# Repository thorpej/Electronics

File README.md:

# Electronics
thorpej's electronics projects repository.  Tube audio, other tube stuff, and stuff with computers in it.

# **WARNING**
Some of the materials in this repository desribe circuits that employ **HIGH VOLTAGES** that can be **LETHAL**.
If you build or otherwise use any of these circuits, you do so **AT YOUR OWN RISK**.

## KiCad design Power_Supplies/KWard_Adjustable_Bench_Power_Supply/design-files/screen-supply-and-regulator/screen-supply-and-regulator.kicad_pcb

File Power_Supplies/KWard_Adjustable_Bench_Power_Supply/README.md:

# Adjustable Bench Power Supply

This is a slight variation on an adjustable regulated bench power supply developed by
Kevin Ward and [documented on the AudioKarma forums](http://audiokarma.org/forums/index.php?threads/adjustable-bench-power-supply-redux.748700/)

The design is essentialy a Maida-style floating regulator that uses an array of 6550 pentodes
as the pass elements rather than a Darlington voltage follower as in the original Maida tech
note.  The 6550s also require a power supply for their screens, which also floats on the B+
rail's output voltage.  A major advantage of using pentode pass elements is the ability to
current-limit the supply, which is a natural result of how pentodes operate.  The current limit
could be adjusted by adjusting the 6550 screen supply voltage, although this feature is not
offered in this build.

There is also a current-limited negative bias supply that provides a nominal 0 - -100V adjustable
voltage range, in addition to an AC filament supply that can provide either 6.3Vac or 12.6Vac.

The main differences between this and Kevin's version are the transformers used.  Kevin's
build uses an Edcor XPWR133 for the B+ rail, floating 6550 screen supply, and the 6550 array's
heaters.  In my build, an AnTek AS-4T400 is used, which necessitates a separate transformer
for the floating 6550 screen supply.  I also opted to use a different transformer for the C-
rail.  Additionally, there are some minor improvements, such as the use of a precision 10-turn
pot for the B+ voltage control (to address a design flaw in the original), as well as an
provision to discharge capacitors on the device-under-test.  The design is otherwise un-changed from Kevin's design.

The interesting files here are:

	1. B+Supply.asc: LTSpice simulation of the B+ rail with the adjustments necessary for the choke and transformer differences.
	2. ScreenSupply.asc: LTSpice simulation of the floating 6550 screen supply with adjustments necessary for a Triad F6-120 transformer.
	3. BiasSupply.asc: LTSpice simulation of the C- rail with adjustments necessary for a Triad F4-120 transformer.
	
The remaining materials are either directly from the AudioKarma thread about Kevin's work (copied
locally for convenience) or Spice models needed for the simulations.

To be added in the future:

	1. Chassis layout drawings.
	2. Control panel CAD file for submitting to Front Panel Express.
	3. Descriptions / photographs of the hand-wired circuit boards.  (What a pain; I should have done proper PCBs...)

## ADDENDUM

I am going to be rebuilding this project using proper PCBs!  Watch here for the KiCad design files!

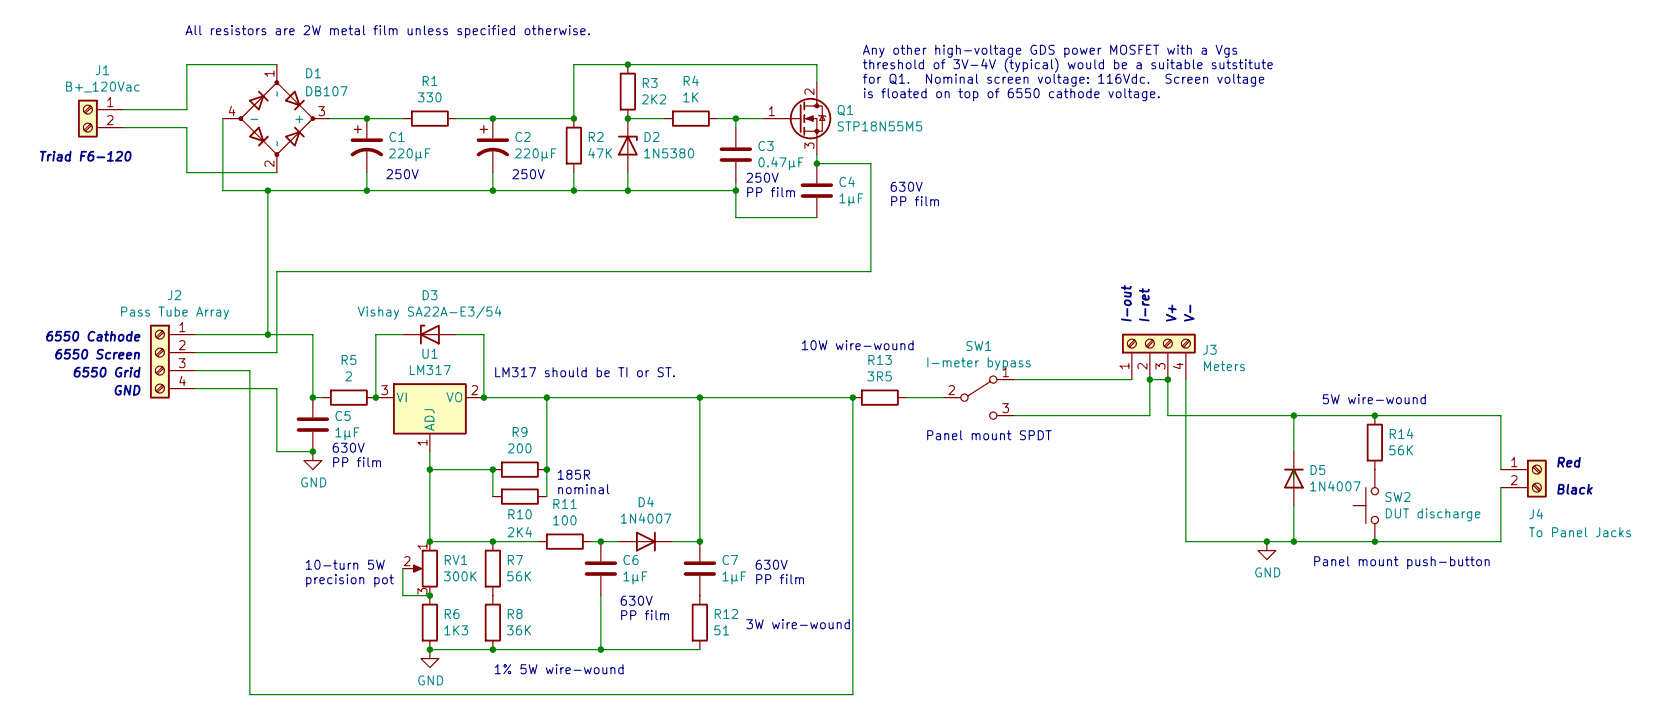
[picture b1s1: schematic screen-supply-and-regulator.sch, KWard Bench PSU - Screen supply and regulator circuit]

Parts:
C1, C2: 220µF; CP_Radial_D18.0mm_P7.50mm; Mouser 647-UCS2E221MHD
C3: 0.47µF; C_Rect_L18.0mm_W8.0mm_P15.00mm_FKS3_FKP3; Mouser 80-PHE426HB6470JR06
C4, C5, C6, C7: 1µF; C_Rect_L18.0mm_W18.0mm_P15.0mm; Mouser 667-ECW-FD2J105PC
D1: DB107; Diode_Bridge_DIP-4_W7.62mm_P5.08mm
D2: 1N5380; D_DO-201_P15.24mm_Horizontal
D3: Vishay SA22A-E3/54; D_DO-15_P15.24mm_Horizontal; Mouser 625-SA22A-E3/54
D4, D5: 1N4007; D_DO-41_SOD81_P10.16mm_Horizontal
J1: B+_120Vac; TerminalBlock_bornier-2_P5.08mm
J2: Pass Tube Array; TE_AMP-4_P10.16mm
J3: Meters; TE_AMP-4_P10.16mm
J4: To Panel Jacks; TE_AMP-2_P10.16mm
Q1: STP18N55M5; TO-220-3_Vertical
R1: 330; R_Axial_DIN0411_L9.9mm_D3.6mm_P15.24mm_Horizontal; Mouser 594-5083NW330R0J
R2: 47K; R_Axial_DIN0411_L9.9mm_D3.6mm_P15.24mm_Horizontal; Mouser 594-5083NW47K00JA100
R3: 2K2; R_Axial_DIN0411_L9.9mm_D3.6mm_P15.24mm_Horizontal; Mouser 594-5083NW2K200J
R4: 1K; R_Axial_DIN0411_L9.9mm_D3.6mm_P15.24mm_Horizontal; Mouser 594-5083NW1K000J
R5: 2; R_Axial_DIN0411_L9.9mm_D3.6mm_P15.24mm_Horizontal; Mouser 594-5083NW2R000J
R6: 1K3; R_Axial_DIN0411_L9.9mm_D3.6mm_P15.24mm_Horizontal; Mouser 594-5083NW1K300J
R7: 56K; R_Axial_Power_L25.0mm_W9.0mm_P30.48mm; Mouser 71-RS00556K00FE12
R8: 36K; R_Axial_Power_L25.0mm_W9.0mm_P30.48mm; Mouser 71-RS00236K00FB12
R9: 200; R_Axial_DIN0411_L9.9mm_D3.6mm_P15.24mm_Horizontal; Mouser 594-5083NW200R0J
R10: 2K4; R_Axial_DIN0411_L9.9mm_D3.6mm_P15.24mm_Horizontal; Mouser 594-5083NW2K400J
R11: 100; R_Axial_DIN0411_L9.9mm_D3.6mm_P15.24mm_Horizontal; Mouser 594-5083NW100R0JA100
R12: 51; R_Axial_DIN0614_L14.3mm_D5.7mm_P20.32mm_Horizontal; Mouser 71-NS02B51R00FE12
R13: 3R5; R_Axial_Power_L48.0mm_W12.5mm_P55.88mm; Mouser 71-RS0103R500FE12
R14: 56K; R_Axial_Power_L25.0mm_W6.4mm_P30.48mm; Mouser 71-CW00556K00JE12
RV1: 300K; TE_AMP-3_P10.16mm
SW1: I-meter bypass; TerminalBlock_bornier-3_P5.08mm
SW2: DUT discharge; TE_AMP-2_P10.16mm
U1: LM317; TO-220-3_Vertical; Mouser 926-LM317AT/NOPB

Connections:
GND: C5.2, C6.2, D5.2 (A), J2.4, J3.4, J4.2, R6.2, R8.2, R12.2, SW2.1
unnamed: C1.1, D1.3 (+), R1.2
unnamed: C1.2, C2.2, C3.2, C4.2, C5.1, D1.4 (-), D2.2 (A), J2.1, R2.2, R5.2
unnamed: C2.1, Q1.2 (D), R1.1, R2.1, R3.1
unnamed: C3.1, Q1.1 (G), R4.1
unnamed: C4.1, J2.2, Q1.3 (S)
unnamed: C6.1, D4.2 (A), R11.1
unnamed: C7.1, D3.2 (A), D4.1 (K), J2.3, R9.1, R10.1, R13.2, U1.2 (VO)
unnamed: C7.2, R12.1
unnamed: D1.1 (~~), J1.1
unnamed: D1.2 (~~), J1.2
unnamed: D2.1 (K), R3.2, R4.2
unnamed: D3.1 (K), R5.1, U1.3 (VI)
unnamed: D5.1 (K), J3.2, J3.3, J4.1, R14.1, SW1.3 (C)
unnamed: J3.1, SW1.1 (A)
unnamed: R6.1, RV1.2, RV1.3
unnamed: R7.2, R8.1
unnamed: R7.1, R9.2, R10.2, R11.2, RV1.1, U1.1 (ADJ)
unnamed: R13.1, SW1.2 (B)
unnamed: R14.2, SW2.2

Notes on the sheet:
Triad F6-120
Any other high-voltage GDS power MOSFET with a Vgs threshold of 3V-4V (typical) would be a suitable sutstitute for Q1. Nominal screen voltage: 116Vdc. Screen voltage is floated on top of 6550 cathode voltage.
6550 Cathode
6550 Grid
6550 Screen
630V PP film
185R nominal
10-turn 5W precision pot
3W wire-wound
1% 5W wire-wound
LM317 should be TI or ST.
All resistors are 2W metal film unless specified otherwise.
10W wire-wound
5W wire-wound
Panel mount SPDT
Panel mount push-button
Red
Black
I-out
I-ret
250V
250V PP film
GND

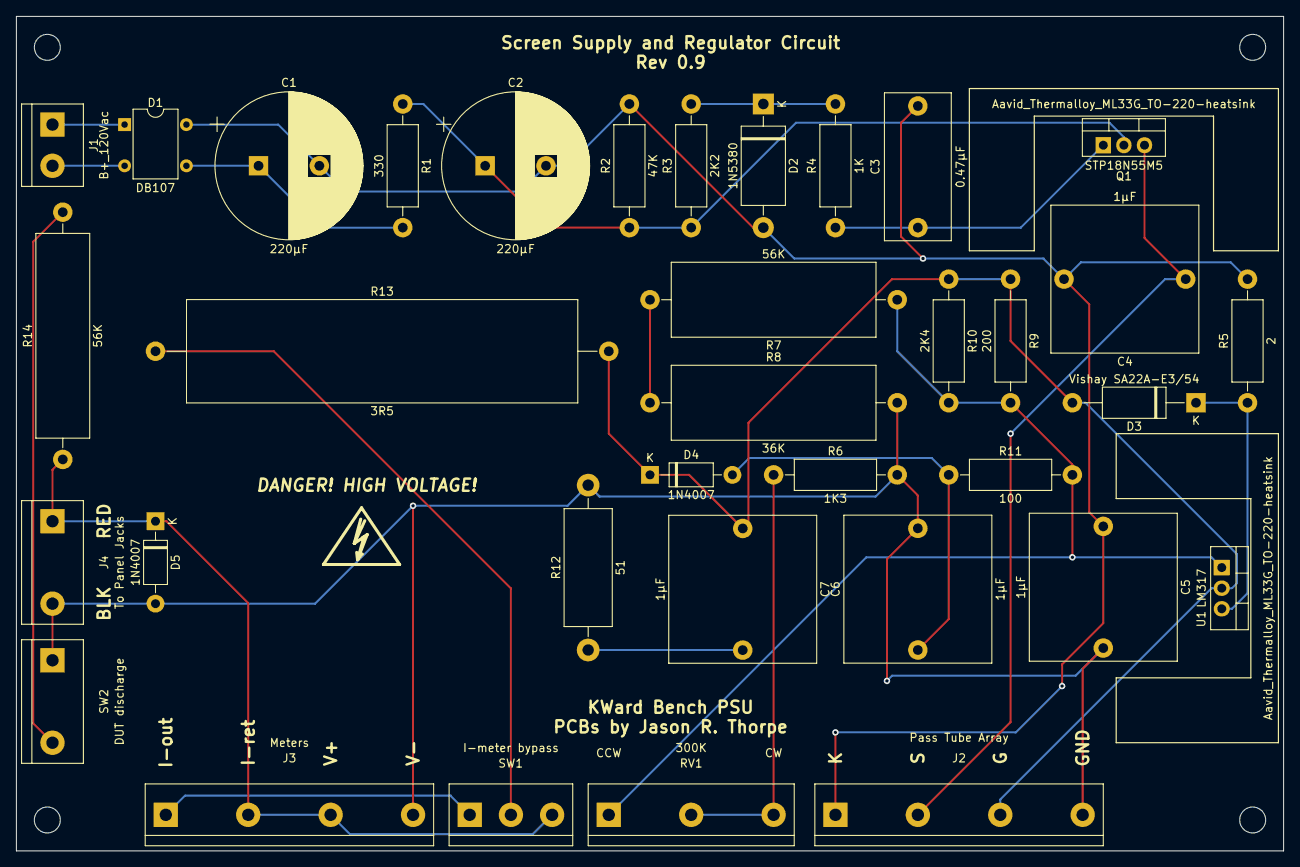
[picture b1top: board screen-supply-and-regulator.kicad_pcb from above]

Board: 2 copper layers, 156.2 x 102.9 mm, 35 parts (0 on the bottom side), 20 nets.

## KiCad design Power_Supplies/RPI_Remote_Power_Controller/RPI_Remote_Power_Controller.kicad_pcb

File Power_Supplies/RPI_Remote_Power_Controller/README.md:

# Remote Power Controller (controlled by Raspberry Pi)

**NOTE: This is provided for informational purposes only.  If you use this information,
or any of these design files, you do so at your own risk.**

This board is for, essentially, a remote-controlled power strip.  A Raspberry Pi Zero W (or a
Banana Pi M2 Zero) controls a Microchip MCP230008 I/O expander over I2C, which in turn drives
the outputs of a pair of ULN2003 Darlington arrays with open-collector outputs (7 on one, 1 on
the other, for a total of 8 outputs).  Each Darlington pair in the ULN2003 features a flyback
diode, making them suitable for driving inductive loads.

The ULN2003 outputs are connected to one end of the coil on a Rayex LB2-12DS-R DPDT relay, the other end being connected to a +12Vdc power supply.  The relay switches are connect to AC Mains input, switching both the hot and neutral leads.

A 12V - 5V @ 5A regulator provides power to the Raspberry Pi Zero W over the 40-pin GPIO header.
The regulator is attached to a relatively beefy Aavid ML33G heat sink.  A 2200µF reservoir
capacitor is provided to handle any transient current surges.

The console UART on the Raspberry Pi is brought out to a sepate 3-pin header on the board
for convenience.

The board will also accommodate a Banana Pi M2 Zero.  This board has the same basic footprint
as the Raspberry Pi Zero W, and also includes built-in WiFi.  The Banana Pi board also has
a compatible GPIO header.  _NOTE: The Banana Pi's console (debug) UART is routed to a separate
pin header on the Banana Pi itself; if you use a Banana Pi, you don't need to use the console
pin header on the power controller board; solder a pin header onto the Banana Pi board, and
use that for console I/O._.

The board's mains input should be fused with a 12A fuse, as that is the current rating of
the Rayex relays, and was used as a design parameter for the PCB.  The mains traces on the
PCB are capable of carrying a 12A load **_if and only if the board is fabricated with
2oz copper_**.  If the board is fabriacated with 1oz copper, then the mains input fuse should be limited to 6A.

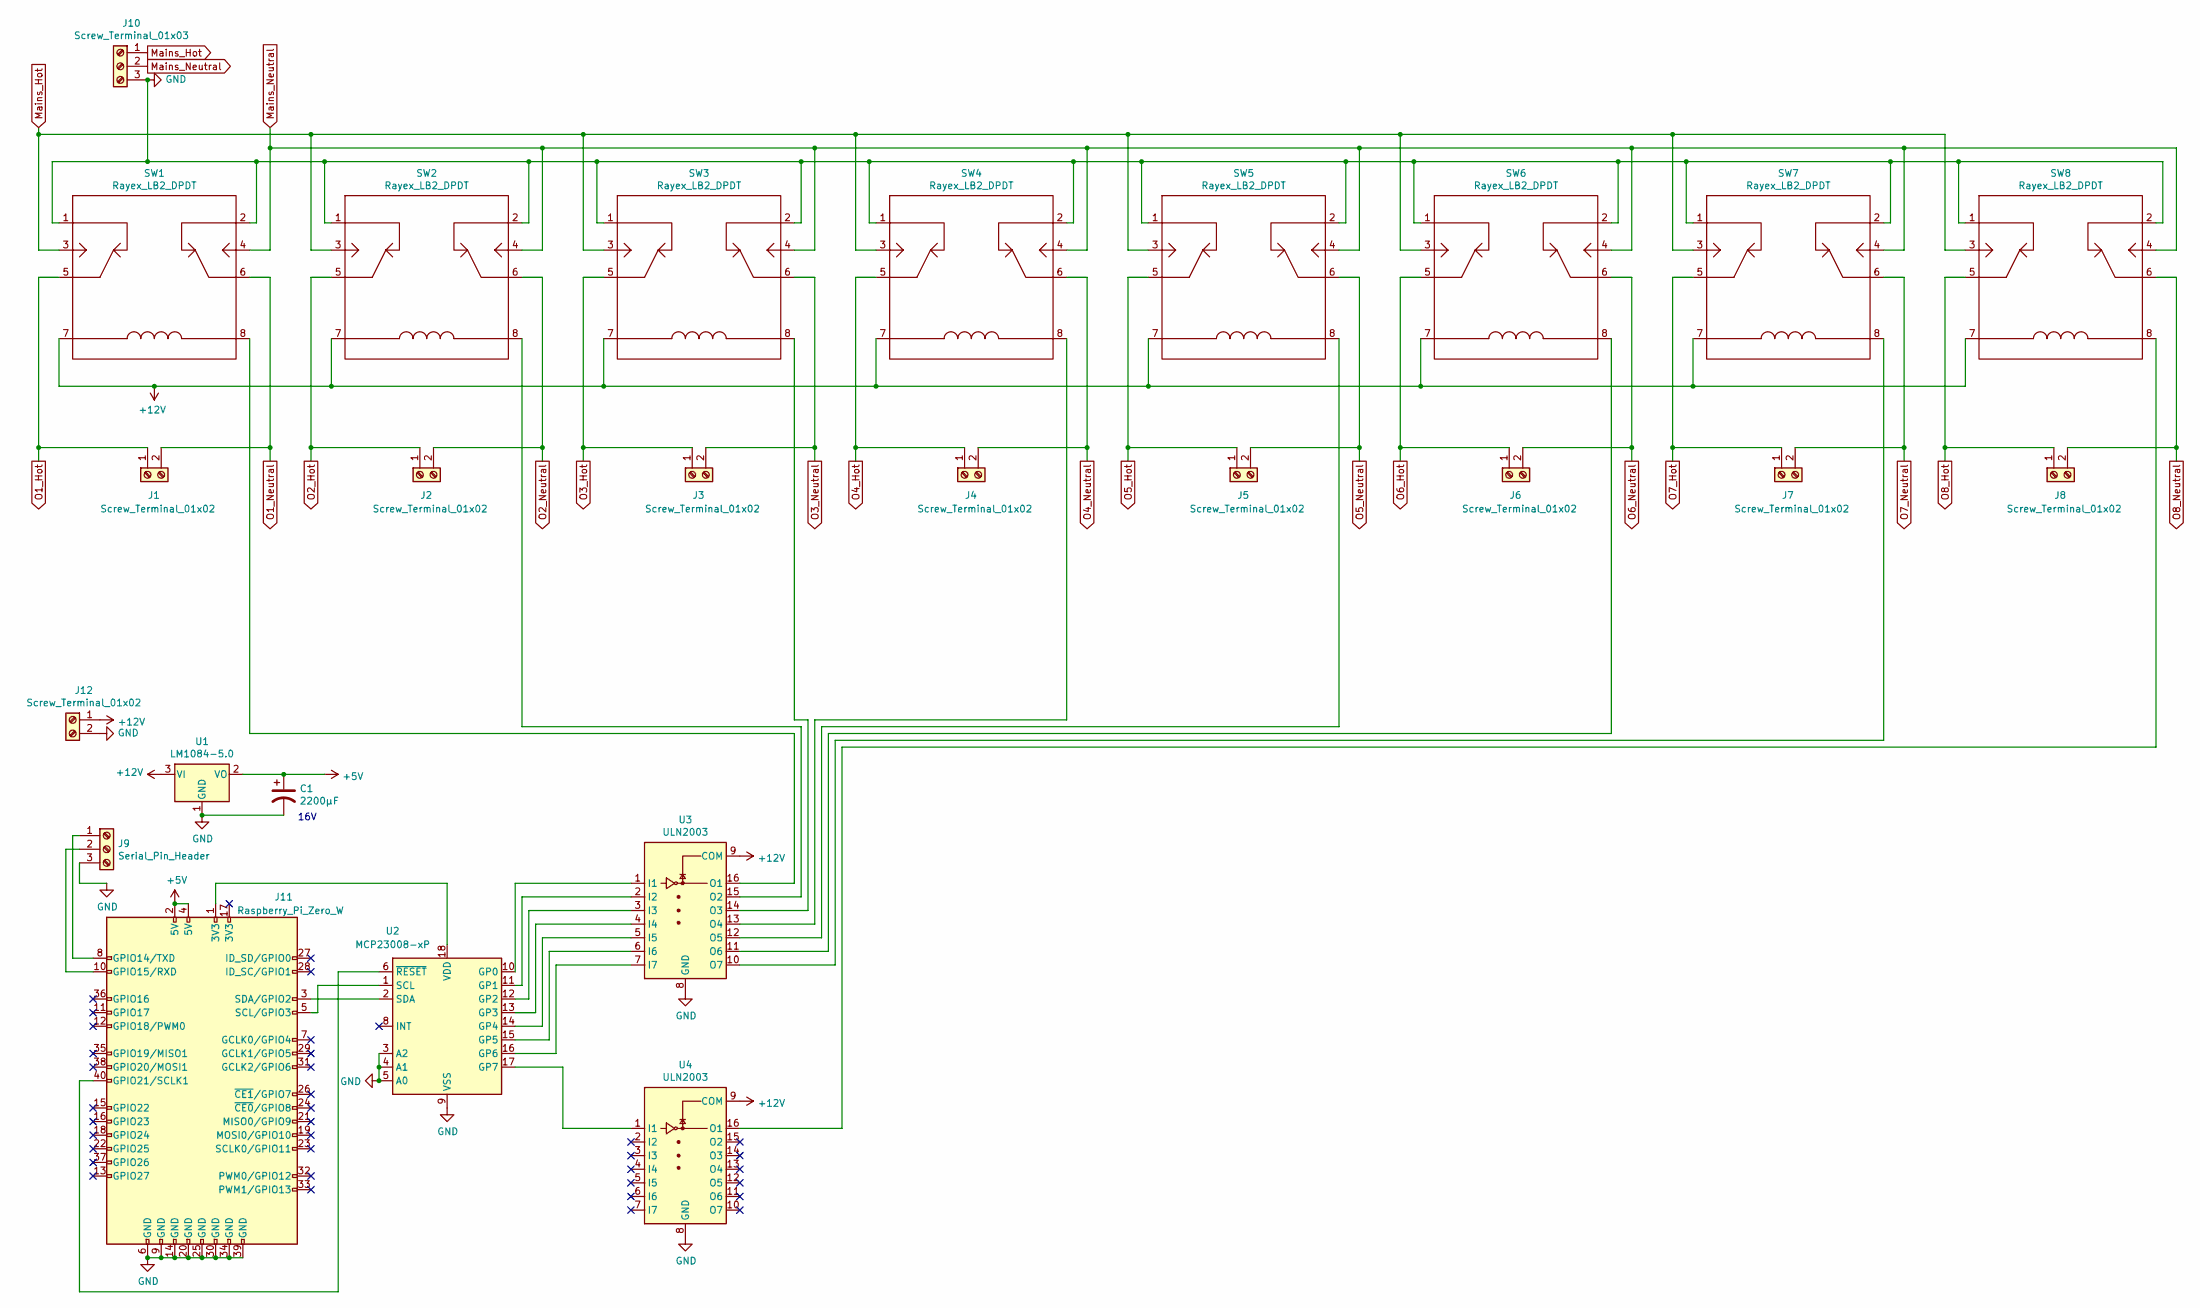
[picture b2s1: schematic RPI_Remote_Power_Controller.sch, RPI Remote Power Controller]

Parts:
C1: 2200µF; CP_Radial_D13.0mm_P5.00mm; Mouser 710-860040378015
J1, J2, J3, J4, J5, J6, J7, J8: Screw_Terminal_01x02; TE_AMP-2_P10.16mm
J9: Serial_Pin_Header; PinHeader_1x03_P2.54mm_Vertical
J10: Screw_Terminal_01x03; TE_AMP-3_P10.16mm
J11: Raspberry_Pi_Zero_W; PinHeader_2x20_P2.54mm_Vertical
J12: Screw_Terminal_01x02; TerminalBlock_bornier-2_P5.08mm
SW1, SW2, SW3, SW4, SW5, SW6, SW7, SW8: Rayex_LB2_DPDT; Rayex-LB2-lug
U1: LM1084-5.0; TO-220-3_Vertical
U2: MCP23008-xP; DIP-18_W7.62mm_Socket
U3, U4: ULN2003; DIP-16_W7.62mm_Socket

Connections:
+5V: C1.1, J11.2 (5V), J11.4 (5V), U1.2 (VO)
+12V: J12.1, SW1.7, SW2.7, SW3.7, SW4.7, SW5.7, SW6.7, SW7.7, SW8.7, U1.3 (VI), U3.9 (COM), U4.9 (COM)
GND: C1.2, J9.3, J10.3, J11.6 (GND), J11.9 (GND), J11.14 (GND), J11.20 (GND), J11.25 (GND), J11.30 (GND), J11.34 (GND), J11.39 (GND), J12.2, SW1.1, SW1.2, SW2.1, SW2.2, SW3.1, SW3.2, SW4.1, SW4.2, SW5.1, SW5.2, SW6.1, SW6.2, SW7.1, SW7.2, SW8.1, SW8.2, U1.1 (GND), U2.3 (A2), U2.4 (A1), U2.5 (A0), U2.9 (VSS), U3.8 (GND), U4.8 (GND)
Mains_Hot: J10.1, SW1.3, SW2.3, SW3.3, SW4.3, SW5.3, SW6.3, SW7.3, SW8.3
Mains_Neutral: J10.2, SW1.4, SW2.4, SW3.4, SW4.4, SW5.4, SW6.4, SW7.4, SW8.4
unnamed: J11.1 (3V3), U2.18 (VDD)
unnamed: J11.3 (SDA/GPIO2), U2.2 (SDA)
unnamed: J11.5 (SCL/GPIO3), U2.1 (SCL)
unnamed: J9.1, J11.8 (GPIO14/TXD)
unnamed: J9.2, J11.10 (GPIO15/RXD)
unnamed: J11.40 (GPIO21/SCLK1), U2.6 (~RESET)
unnamed: SW1.8, U3.16 (O1)
unnamed: SW2.8, U3.15 (O2)
unnamed: SW3.8, U3.14 (O3)
unnamed: SW4.8, U3.13 (O4)
unnamed: SW5.8, U3.12 (O5)
unnamed: SW6.8, U3.11 (O6)
unnamed: SW7.8, U3.10 (O7)
unnamed: SW8.8, U4.16 (O1)
unnamed: U2.10 (GP0), U3.1 (I1)
unnamed: U2.11 (GP1), U3.2 (I2)
unnamed: U2.12 (GP2), U3.3 (I3)
unnamed: U2.13 (GP3), U3.4 (I4)
unnamed: U2.14 (GP4), U3.5 (I5)
unnamed: U2.15 (GP5), U3.6 (I6)
unnamed: U2.16 (GP6), U3.7 (I7)
unnamed: U2.17 (GP7), U4.1 (I1)
O1_Hot: J1.1, SW1.5
O1_Neutral: J1.2, SW1.6
O2_Hot: J2.1, SW2.5
O2_Neutral: J2.2, SW2.6
O3_Hot: J3.1, SW3.5
O3_Neutral: J3.2, SW3.6
O4_Hot: J4.1, SW4.5
O4_Neutral: J4.2, SW4.6
O5_Hot: J5.1, SW5.5
O5_Neutral: J5.2, SW5.6
O6_Hot: J6.1, SW6.5
O6_Neutral: J6.2, SW6.6
O7_Hot: J7.1, SW7.5
O7_Neutral: J7.2, SW7.6
O8_Hot: J8.1, SW8.5
O8_Neutral: J8.2, SW8.6

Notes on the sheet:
16V

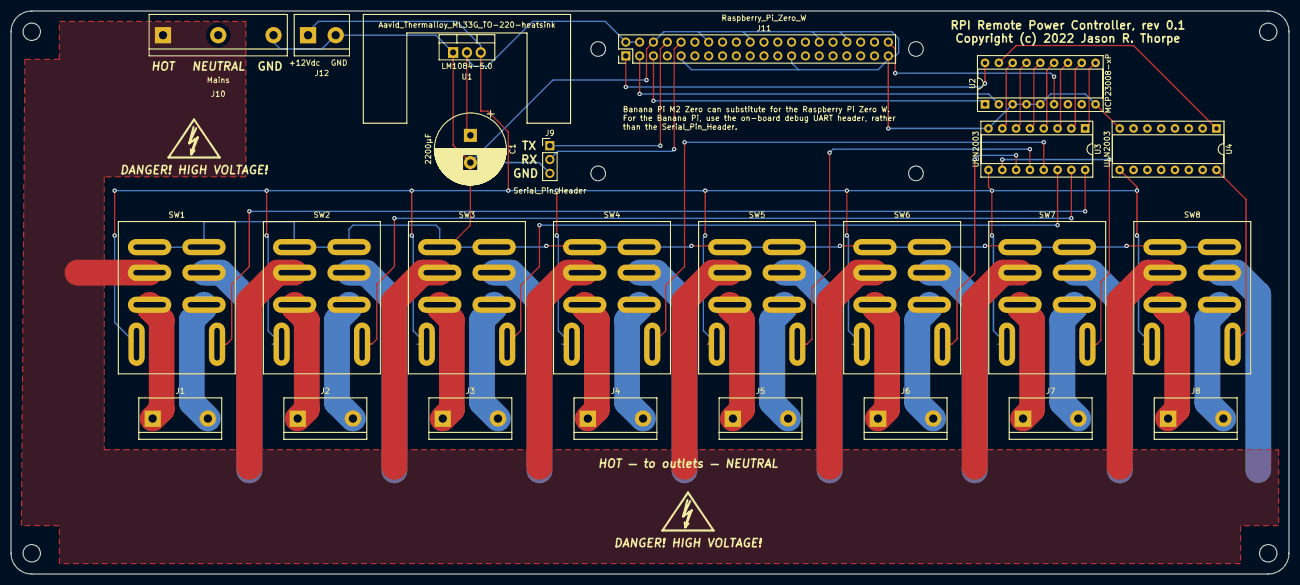
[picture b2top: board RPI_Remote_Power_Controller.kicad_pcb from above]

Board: 2 copper layers, 234.9 x 103.5 mm, 25 parts (0 on the bottom side), 43 nets.

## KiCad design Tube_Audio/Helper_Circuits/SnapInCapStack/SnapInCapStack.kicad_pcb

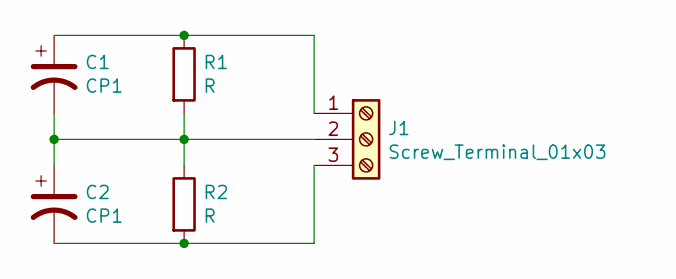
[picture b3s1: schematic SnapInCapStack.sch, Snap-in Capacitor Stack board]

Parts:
C1, C2: CP1; CP_Radial_D35.0mm_P10.00mm_3pin_SnapIn
J1: Screw_Terminal_01x03; TE_AMP-3_P10.16mm
R1, R2: R; R_Axial_DIN0414_L11.9mm_D4.5mm_P5.08mm_Vertical

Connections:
unnamed: C1.1, J1.1, R1.1
unnamed: C1.2, C2.1, J1.2, R1.2, R2.1
unnamed: C2.2, J1.3, R2.2

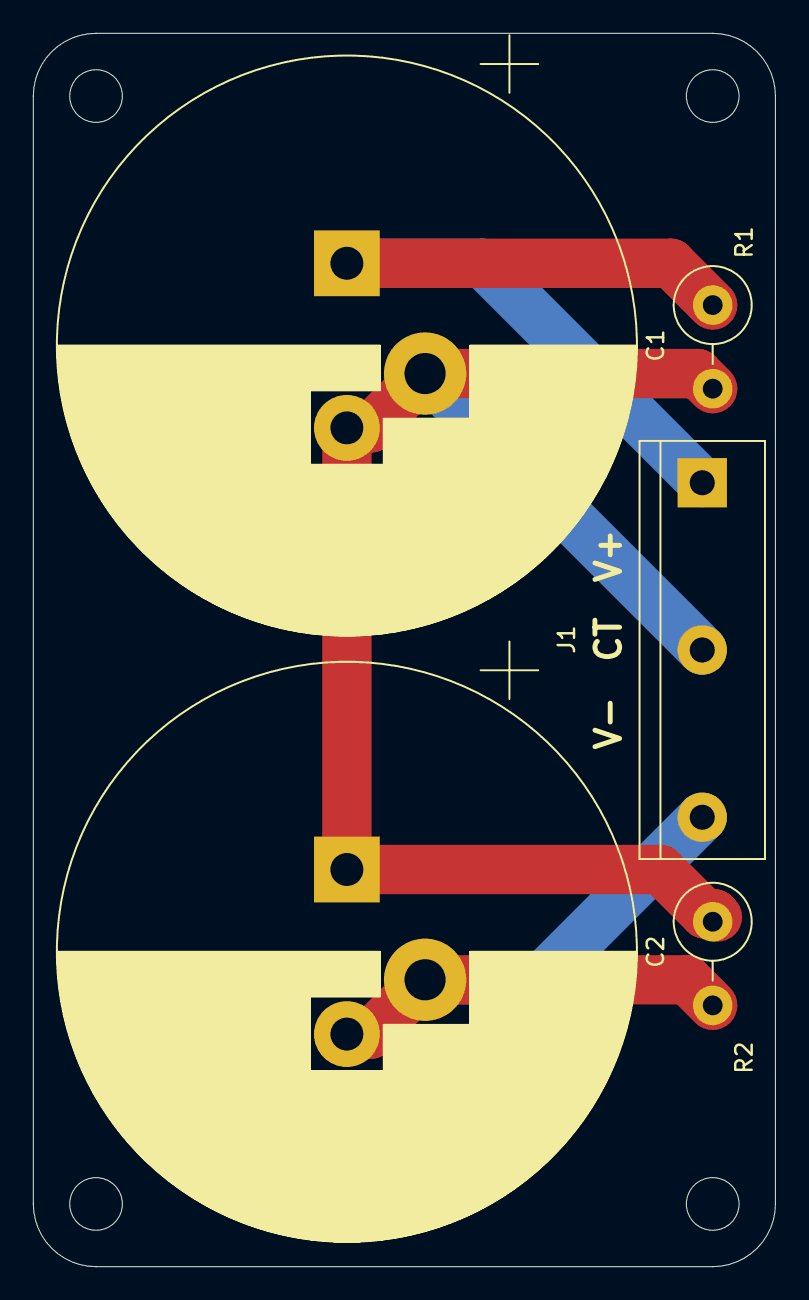
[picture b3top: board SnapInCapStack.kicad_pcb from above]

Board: 2 copper layers, 45.1 x 74.9 mm, 5 parts (0 on the bottom side), 3 nets.

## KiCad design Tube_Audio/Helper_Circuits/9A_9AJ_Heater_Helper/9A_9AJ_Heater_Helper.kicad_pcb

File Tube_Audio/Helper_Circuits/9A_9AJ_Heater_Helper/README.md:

# 9A / 9AJ Heater Helper

This is a simple helper board that makes it easy to wire up a 9-pin tube
socket to work with either 12AX7 / ECC83 or the Russian 6N2P.  The 6N2P
is nearly identical to the 12AX7 except for it's heater configuration and
the presence of an internal shield that needs to be grounded.

This uses one of those small appliance voltage selector switches that are
typically use to connect the incoming mains line cord to either the 120V
or 240V windings of a power tranformer.  I selected this switch because it's
small and has a recessed slider, whic makes it more difficult to change the
setting accidentally.  The particular switch I selected is the C&K V80212MS02Q,
which is readily available from Mouser.  You might find another switch that's
compatible.

Besides the switch, you just need a couple of standard 3-position terminal
blocks and some M3 screws and stand-offs.  The board measures roughly
1.25 inches by 2.25 inches, so it's pretty small and easy to tuck into
the corner of your project.

Enjoy!

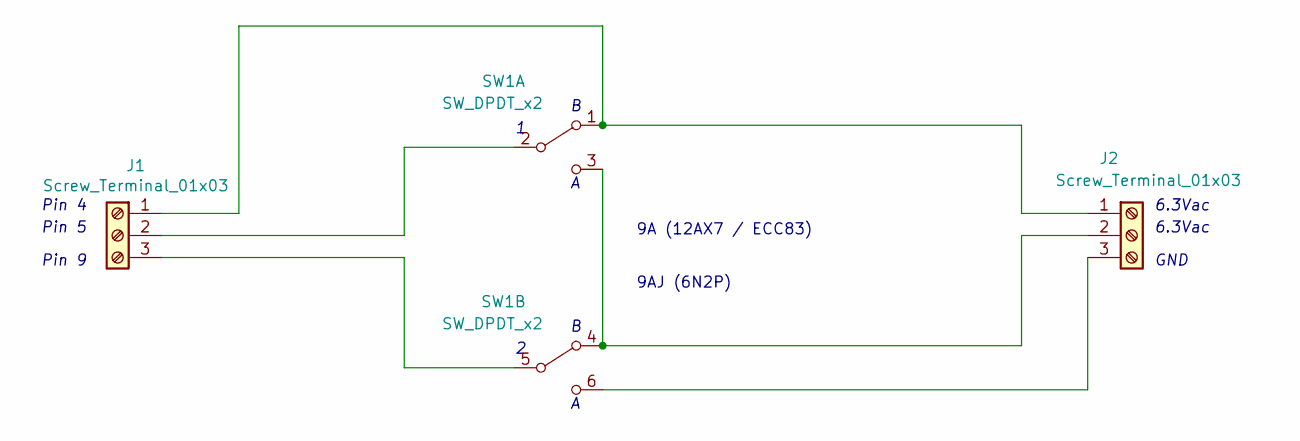
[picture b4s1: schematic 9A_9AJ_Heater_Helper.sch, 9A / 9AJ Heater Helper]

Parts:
J1, J2: Screw_Terminal_01x03; TerminalBlock_bornier-3_P5.08mm
SW1: SW_DPDT_x2; SW_SPDT_CandK-V80212MS02Q; Part C&K V80212MS02Q

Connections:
unnamed: J1.1, J2.1, SW1.1 (A)
unnamed: J1.2, SW1.2 (B)
unnamed: J1.3, SW1.5 (B)
unnamed: J2.2, SW1.3 (C), SW1.4 (A)
unnamed: J2.3, SW1.6 (C)

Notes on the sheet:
9A (12AX7 / ECC83) 9AJ (6N2P)
Pin 4
Pin 5
Pin 9
GND
6.3Vac

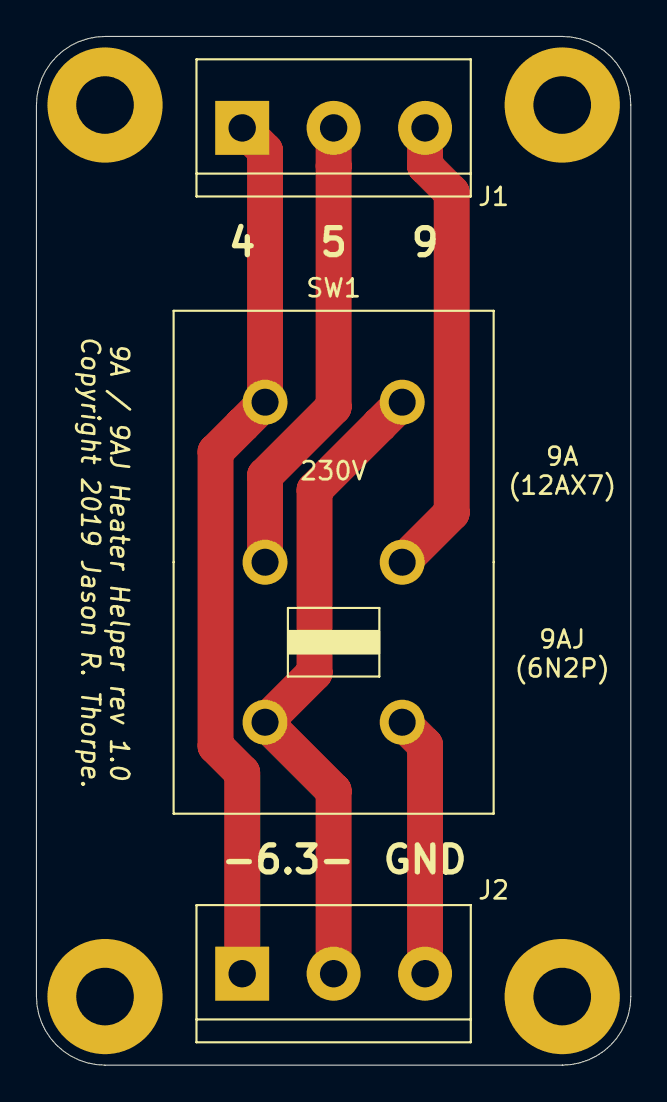
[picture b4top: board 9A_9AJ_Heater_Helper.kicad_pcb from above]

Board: 2 copper layers, 33.0 x 57.2 mm, 3 parts (0 on the bottom side), 5 nets.

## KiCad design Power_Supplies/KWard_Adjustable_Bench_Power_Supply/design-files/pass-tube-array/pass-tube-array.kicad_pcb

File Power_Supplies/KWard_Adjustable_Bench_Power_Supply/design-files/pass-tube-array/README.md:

# Pass tube array

The pass tube array board holds the 6550 pentodes that are used as the
pass element for the Maida regulator on the [screen supply and regulator
board](../screen-supply-and-regulator).

This board is incredibly simple.  On one end of the board are terminals
for the 4 connections made to a beam pentode:

* Anodes / plates (_A_)
* Screens / G2 (S)
* Cathodes (K)
* Control grids (G)

The _A_ terminal connects to the output of the [B+ supply](../hv-supply).
The _S_, _K_, and _G_ terminals connect to the corresponding terminals on
the [screen supply and regulator board](../screen-supply-and-regulator).

On the other end of the board are terminals for the 6.3Vac filament supply
provided by the AkTek AS-4T400 power transformer that powers the B+ supply.

The board itself holds between 1 and 4 6550 pentodes, which are wired in
parallel.  Each 6550 supplies 100mA of current for the PSU output.  The
tubes installed should be a matched set so that they share the current
roughly equally.  A 10 Ohm ballast resistor in series with each 6550 cathode
aids in load sharing.

Each 6550 also contains a 150 Ohm screen protection resistor, in addition
to a 1K Ohm grid stopper resistor to suppress any oscillation.

The board has standard M3 mounting holes (one in each corner plus one in
the center), and is intended to be mounted in a location convenient to the
screen supply and regulator board.  The board should be mounted such that
the 6550s are in a vertical position.  The 12V DC fan should be mounted
such as to provide forced-air cooling to the pass tube array.

The board includes a virtual center tap to float the 6550 filament supply
on top of the 6550 cathode voltage.

## Parts list

Note that all resistors are 2W metal film unless specified otherwise.  The Mouser
part numbers provided here for standard resistors are for Vishay PR02-series, which
fit the footprints on the board.

* 4x PCB-mount octal tube sockets, [AES P-ST8-193](https://www.tubesandmore.com/products/socket-8-pin-octal-ceramic-pc-mount) or
equivalent (26mm pin circle diameter, 2mm pin width).
* 1x 2-position screw terminal block, 5.08mm pitch (CUI TB007-508-02BE or equivalent).
_Mouser part number 490-TB007-508-02BE._
* 1x 4-position screw terminal block, 10.16mm pitch (Molex 39910-0104 or equivalent).
_Mouser part number 538-39910-0104._
* 4x 1K Ohm resistors.
_Mouser part number 594-5083NW1K000J._
* 4x 150 Ohm resistors.
_Mouser part number 594-5083NW150R0J._
* 4x 10 Ohm resistors.
_Mouser part number 594-5083NW10R00J._
* 2x 220 Ohm resistors.
_Mouser part number 594-5083NW220R0J._

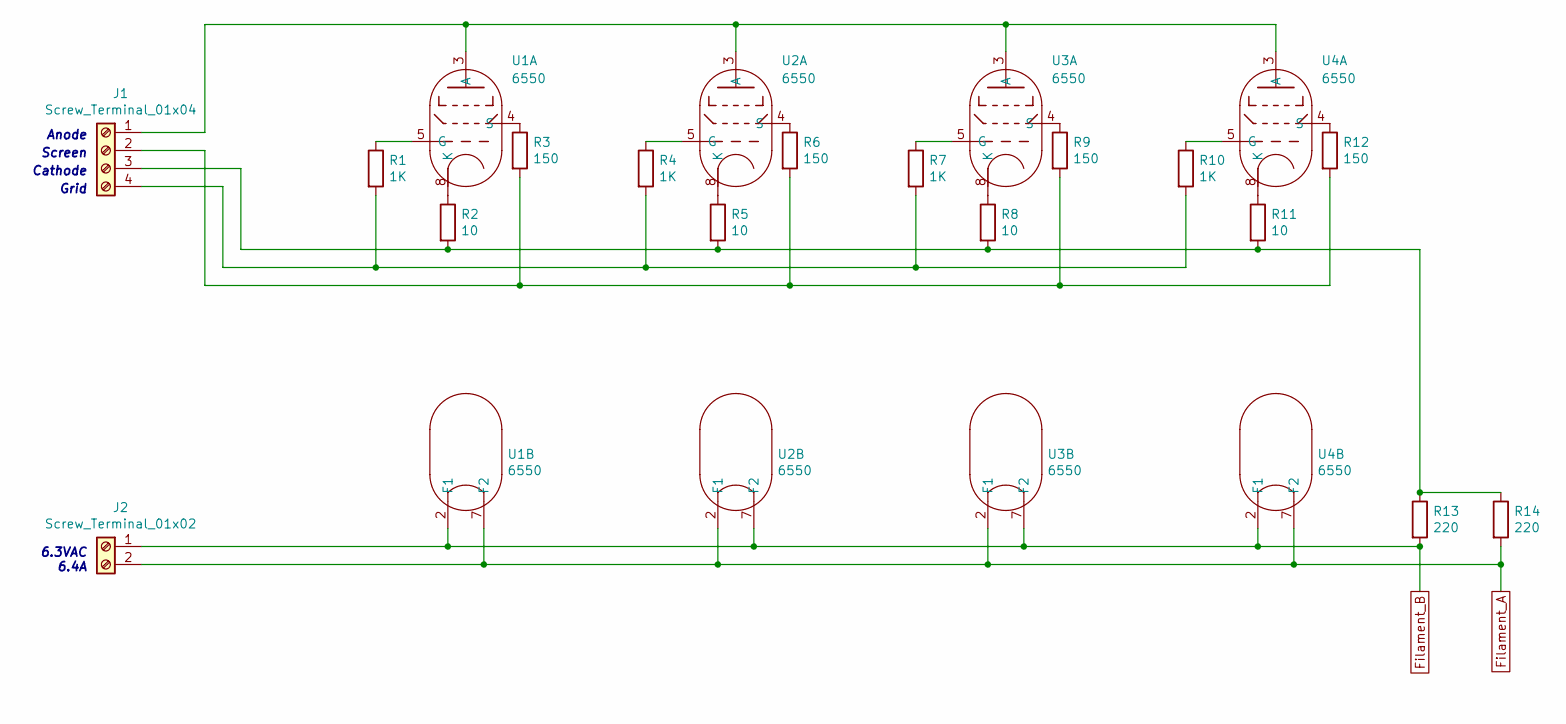
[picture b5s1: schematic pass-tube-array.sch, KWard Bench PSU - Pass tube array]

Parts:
J1: Screw_Terminal_01x04; TE_AMP-4_P10.16mm
J2: Screw_Terminal_01x02; TerminalBlock_bornier-2_P5.08mm
R1, R4, R7, R10: 1K; R_Axial_DIN0411_L9.9mm_D3.6mm_P15.24mm_Horizontal; Mouser 594-5083NW1K000J
R2, R5, R8, R11: 10; R_Axial_DIN0411_L9.9mm_D3.6mm_P15.24mm_Horizontal; Mouser 594-5083NW10R00J
R3, R6, R9, R12: 150; R_Axial_DIN0411_L9.9mm_D3.6mm_P15.24mm_Horizontal; Mouser 594-5083NW150R0J
R13, R14: 220; R_Axial_DIN0411_L9.9mm_D3.6mm_P15.24mm_Horizontal; Mouser 594-5083NW220R0J
U1, U2, U3, U4: 6550; AES_P-ST8-193_Octal_T14

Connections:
Filament_A: J2.2, R14.2, U1.7 (F2), U2.2 (F1), U3.2 (F1), U4.7 (F2)
Filament_B: J2.1, R13.2, U1.2 (F1), U2.7 (F2), U3.7 (F2), U4.2 (F1)
unnamed: J1.1, U1.3 (A), U2.3 (A), U3.3 (A), U4.3 (A)
unnamed: J1.2, R3.2, R6.2, R9.2, R12.2
unnamed: J1.3, R2.2, R5.2, R8.2, R11.2, R13.1, R14.1
unnamed: J1.4, R1.2, R4.2, R7.2, R10.2
unnamed: R1.1, U1.5 (G)
unnamed: R2.1, U1.8 (K)
unnamed: R3.1, U1.4 (S)
unnamed: R4.1, U2.5 (G)
unnamed: R5.1, U2.8 (K)
unnamed: R6.1, U2.4 (S)
unnamed: R7.1, U3.5 (G)
unnamed: R8.1, U3.8 (K)
unnamed: R9.1, U3.4 (S)
unnamed: R10.1, U4.5 (G)
unnamed: R11.1, U4.8 (K)
unnamed: R12.1, U4.4 (S)

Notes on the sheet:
Anode
Screen
Grid
Cathode
6.3VAC 6.4A

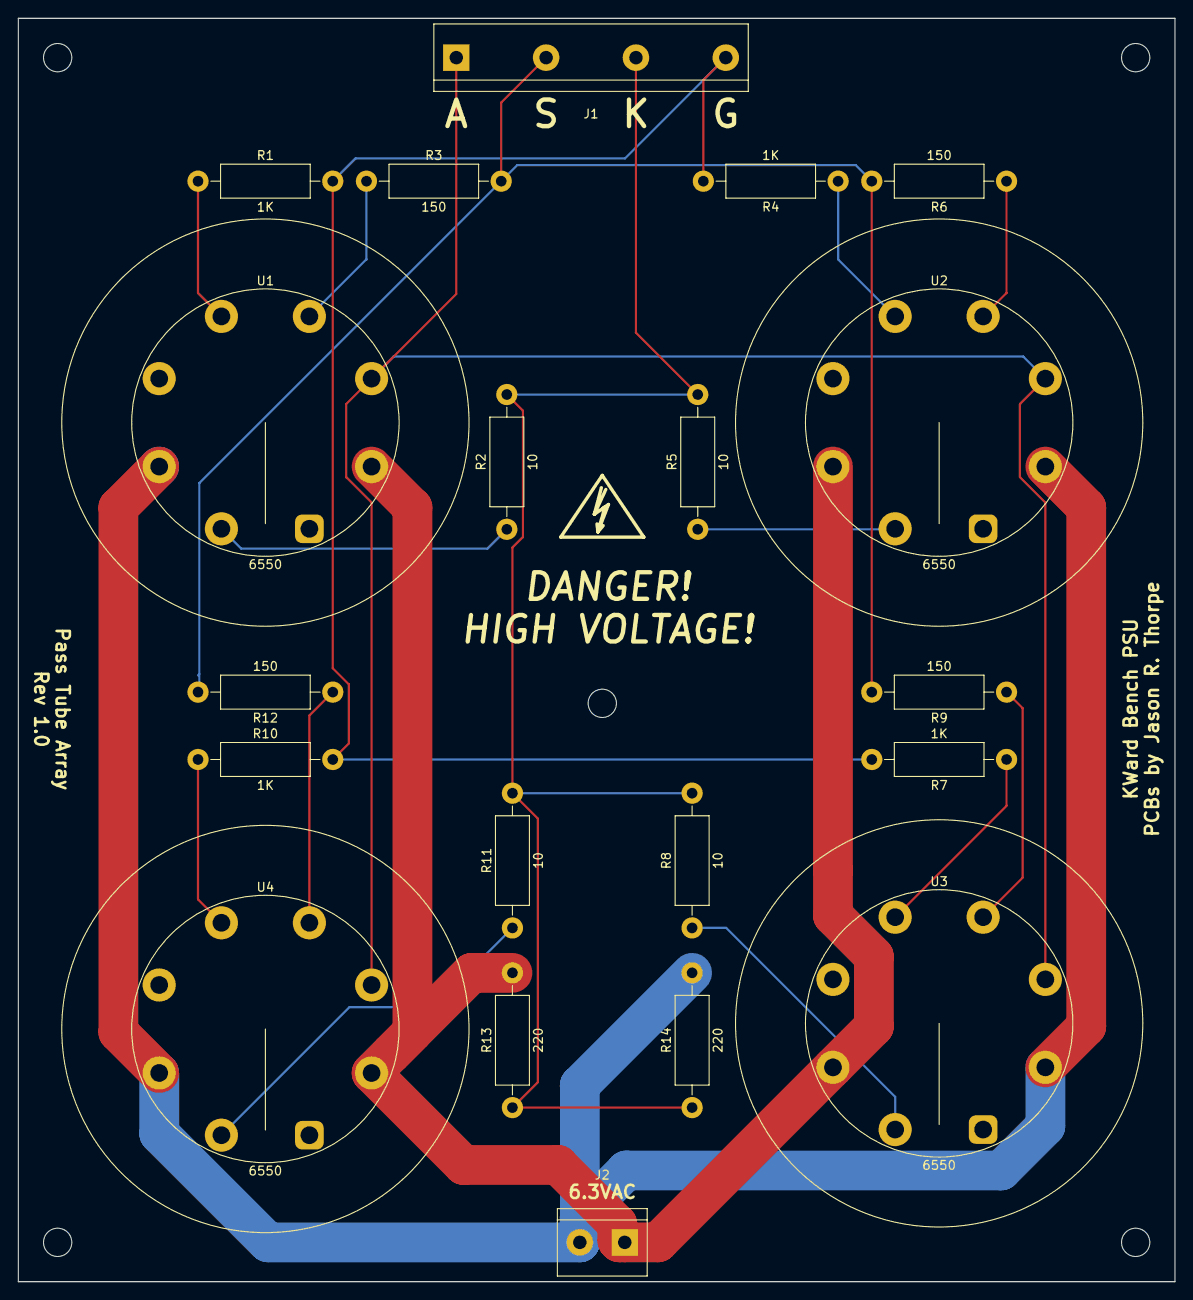
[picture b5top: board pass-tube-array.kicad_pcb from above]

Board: 2 copper layers, 130.8 x 142.9 mm, 20 parts (0 on the bottom side), 18 nets.

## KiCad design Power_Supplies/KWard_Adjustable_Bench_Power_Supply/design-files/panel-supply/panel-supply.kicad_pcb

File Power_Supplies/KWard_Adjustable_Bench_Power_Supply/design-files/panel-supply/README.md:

# Panel supply

The panel supply board provides a regulated supply to the pass tube array's
cooling fan and the PSU's meters: B+ voltage, B+ current, and C- voltage.

The board is powered by a 12Vac @ 1A transformer, such as the Triad F5-12.
The AC input is rectified by a Rectron DB101 diode bridge chip, filtered,
and fed to an LM2940 12V LDO regulator.

The 12Vdc output for the cooling fan has a provision for a resistor that can
be used to limit the current or drop the voltage to the fan, if desired.  If
you don't want to put a resistor there, just install a jumper wire at the R1
position.  Note the resistor is mounted vertically (to save board space).

The board also has a provisions for 3 Murata MEE1S12xxDC DC-DC converters.
Even if your meters can operate on 12Vdc, use of these DC-DC converters is
**mandatory** because the inexpensive panel meters widely available from China
typically require isolated power supplies.  (Speculation: they are floating
their own internal supply on top of measured voltage?)

There is room on the board for a small heat sink for the LM2940, if necessary,
although there is no dedicated footprint outline for it.  If your LM2940 is
getting warm, there are a variety of heat sinks availble from outlets such as
Amazon (just search for "TO-220 heatsink") that should fit in the alotted space.

The board has standard M3 mounting holes, and is intended to be mounted on the
back of the PSU front panel using stand-offs.

## Parts list

* 12Vac @ 1A power transformer, such as the Triad F5-12.
_Mouser part number 553-F5-12._
* 5x 2-position screw terminal blocks, 2.54mm pitch (TE 282834-2 or equivalent).
_Mouser part number 571-282834-2._
* 1x Rectron DB101 diode bridge (any Rectron DB10x can substitute, if desired).
_Mouser part number 583-DB101._
* 1x 2200µF 25V electrolytic capacitor, up to 12.5mm diameter, 5mm lead spacing.
_Mouser part number 555-RJH-25V222MI9#._
* 1x 220µf 25V electrolytic capacitor, up to 6.3mm diameter, 2.5mm lead spacing.
This capacitor should have an ESR between 100 mOhm and 1 Ohm, per the LM2940 data
sheet.  _Mouser part number 232-25YXS220MEFC63X1._
* 1x LM2940 12V 1A LDO regulator or equivalent (see LM2940 data sheet for pinout).
_Mouser part number 926-LM2940T-50/LF08._
* Murata MEE1S12xxDC DC-DC converters (availble from Mouser or DigiKey).

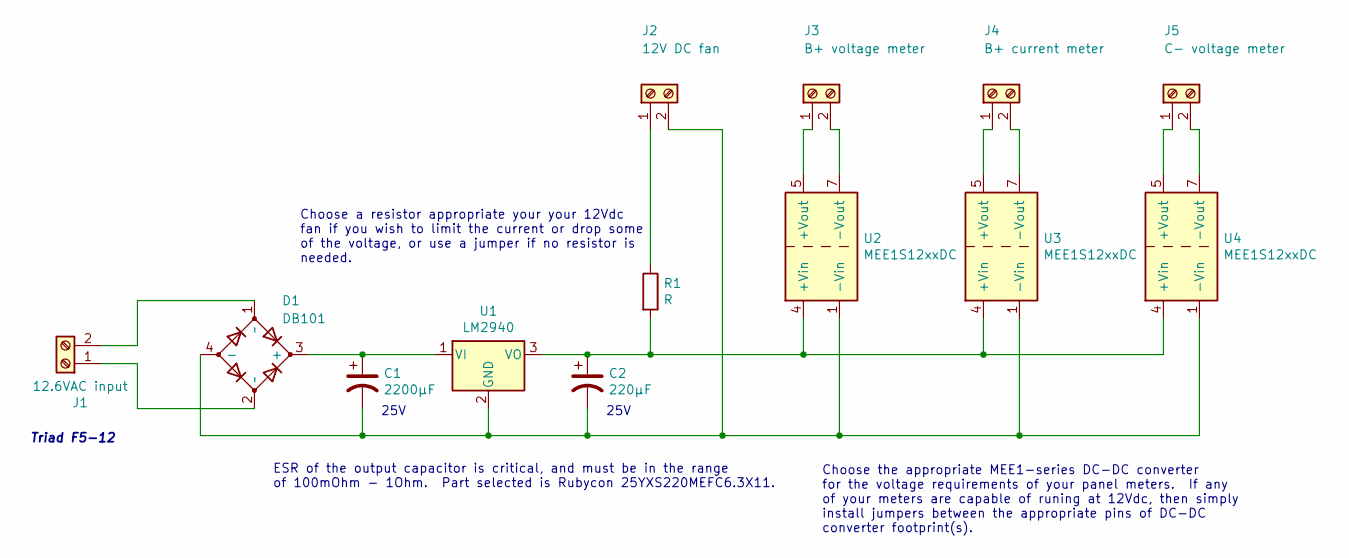
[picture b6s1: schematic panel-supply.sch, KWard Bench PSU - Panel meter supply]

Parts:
C1: 2200µF; CP_Radial_D12.5mm_P5.00mm; Mouser 555-RJH-25V222MI9#
C2: 220µF; CP_Radial_D6.3mm_P2.50mm; Mouser 232-25YXS220MEFC63X1
D1: DB101; Diode_Bridge_DIP-4_W7.62mm_P5.08mm; Mouser 583-DB101
J1: 12.6VAC input; TerminalBlock_TE_282834-2_1x02_P2.54mm_Horizontal
J2: 12V DC fan; TerminalBlock_TE_282834-2_1x02_P2.54mm_Horizontal
J3: B+ voltage meter; TerminalBlock_TE_282834-2_1x02_P2.54mm_Horizontal
J4: B+ current meter; TerminalBlock_TE_282834-2_1x02_P2.54mm_Horizontal
J5: C- voltage meter; TerminalBlock_TE_282834-2_1x02_P2.54mm_Horizontal
R1: R; R_Axial_DIN0309_L9.0mm_D3.2mm_P2.54mm_Vertical
U1: LM2940; TO-220-3_Vertical
U2, U3, U4: MEE1S12xxDC; DIP-8_W7.62mm

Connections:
unnamed: C1.1, D1.3 (+), U1.1 (VI)
unnamed: C1.2, C2.2, D1.4 (-), J2.2, U1.2 (GND), U2.1 (-Vin), U3.1 (-Vin), U4.1 (-Vin)
unnamed: C2.1, R1.2, U1.3 (VO), U2.4 (+Vin), U3.4 (+Vin), U4.4 (+Vin)
unnamed: D1.1 (~~), J1.2
unnamed: D1.2 (~~), J1.1
unnamed: J2.1, R1.1
unnamed: J3.1, U2.5 (+Vout)
unnamed: J3.2, U2.7 (-Vout)
unnamed: J4.1, U3.5 (+Vout)
unnamed: J4.2, U3.7 (-Vout)
unnamed: J5.1, U4.5 (+Vout)
unnamed: J5.2, U4.7 (-Vout)

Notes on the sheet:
25V
Choose the appropriate MEE1-series DC-DC converter for the voltage requirements of your panel meters. If any of your meters are capable of runing at 12Vdc, then simply install jumpers between the appropriate pins of DC-DC converter footprint(s).
Choose a resistor appropriate your your 12Vdc fan if you wish to limit the current or drop some of the voltage, or use a jumper if no resistor is needed.
ESR of the output capacitor is critical, and must be in the range of 100mOhm - 1Ohm. Part selected is Rubycon 25YXS220MEFC6.3X11.
Triad F5-12

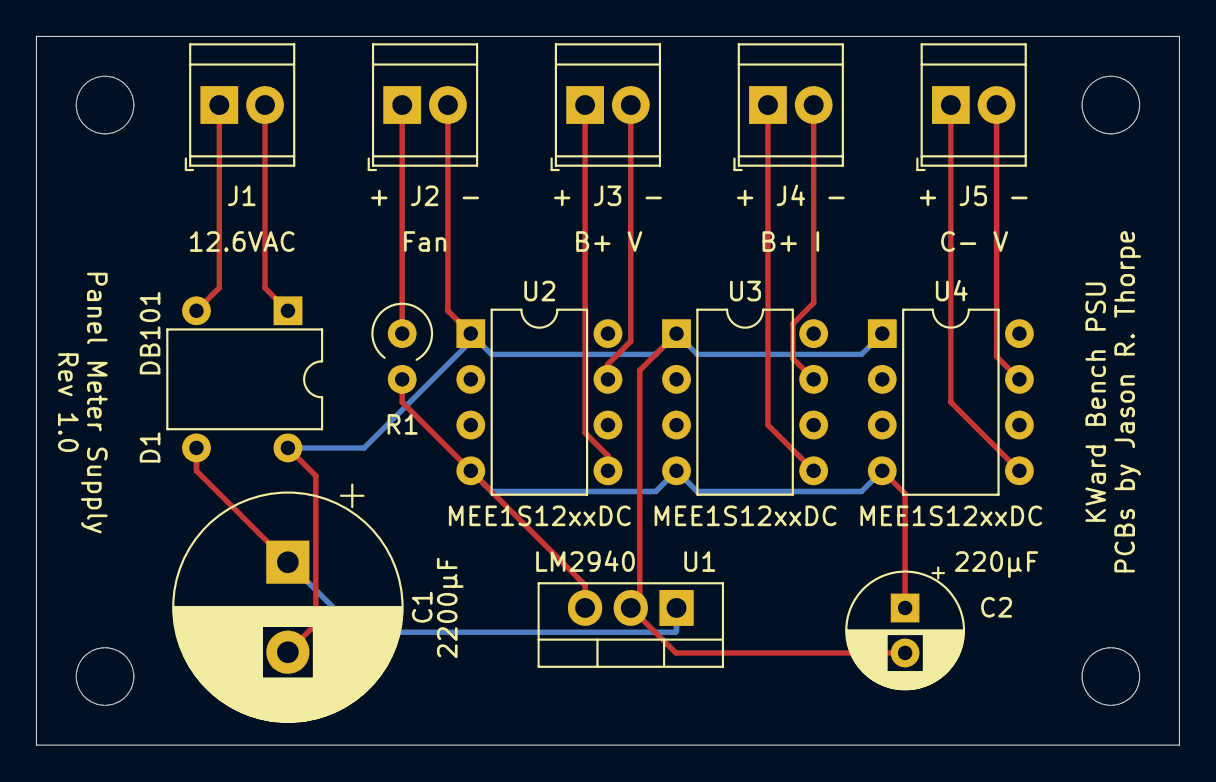
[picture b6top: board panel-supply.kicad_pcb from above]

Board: 2 copper layers, 63.5 x 39.4 mm, 13 parts (0 on the bottom side), 12 nets.

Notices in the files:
Misc_Audio/RAdLib/Bus_Interface.sch:
Copyright 2019 Jason R. Thorpe.  All rights reserved.
See LICENSE.txt.
Power_Supplies/KWard_Adjustable_Bench_Power_Supply/design-files/bias-supply/bias-supply.kicad_pcb:
Copyright (c) 2021 Jason R. Thorpe. See LICENSE.
Power_Supplies/KWard_Adjustable_Bench_Power_Supply/design-files/bias-supply/bias-supply.sch:
Copyright (c) 2017-2022 Kevin Ward and Jason R. Thorpe. See LICENSE.
Power_Supplies/KWard_Adjustable_Bench_Power_Supply/design-files/panel-supply/panel-supply.kicad_pcb:
Copyright (c) 2021-2022 Jason R. Thorpe. See LICENSE.
